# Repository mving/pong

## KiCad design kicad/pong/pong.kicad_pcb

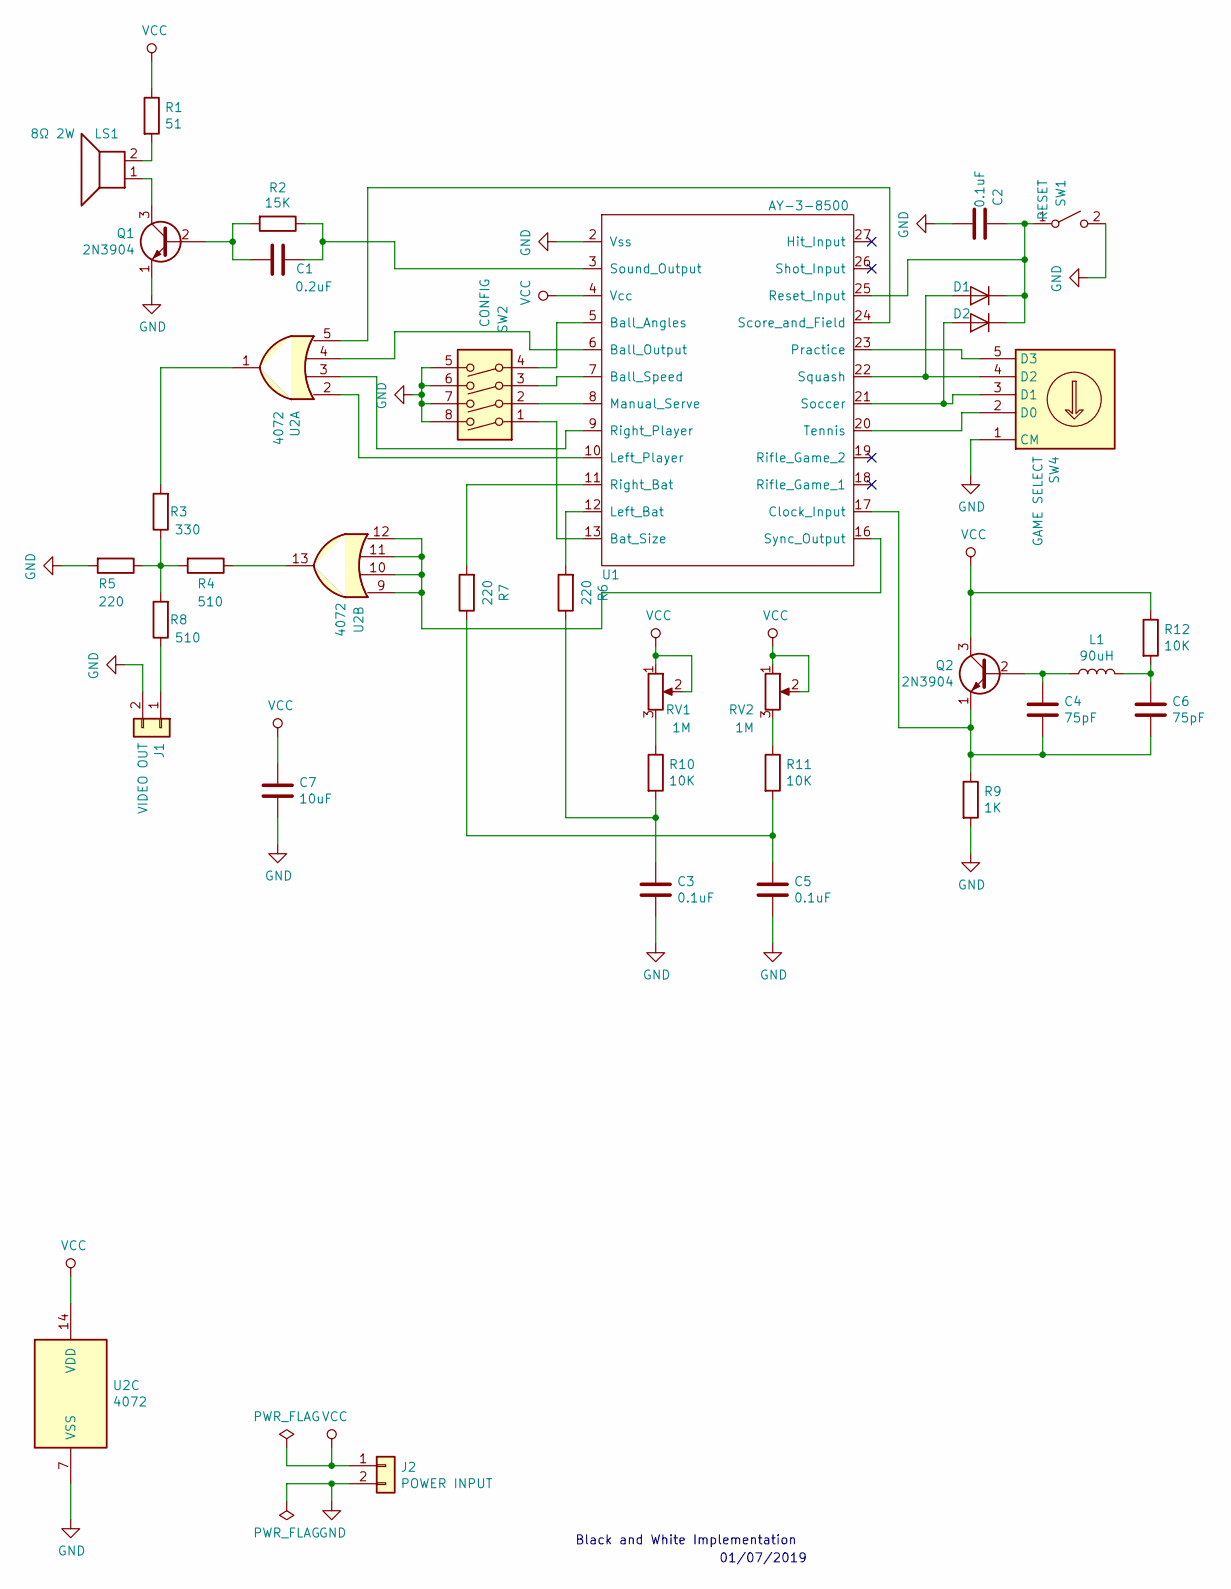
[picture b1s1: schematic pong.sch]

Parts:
C1: 0.2uF; C_Disc_D3.8mm_W2.6mm_P2.50mm
C2, C3, C5: 0.1uF; C_Disc_D3.8mm_W2.6mm_P2.50mm
C4, C6: 75pF; C_Disc_D3.8mm_W2.6mm_P2.50mm
C7: 10uF; C_Radial_D4.0mm_H5.0mm_P1.50mm
D1, D2: D; D_DO-35_SOD27_P7.62mm_Horizontal
J1: VIDEO OUT; rca_white
J2: POWER INPUT; BarrelJack_CUI_PJ-063AH_Horizontal
L1: 90uH; L_Axial_L5.3mm_D2.2mm_P10.16mm_Horizontal_Vishay_IM-1
LS1: 8Ω 2W; PinHeader_1x02_P2.00mm_Horizontal
Q1, Q2: 2N3904; TO-92_HandSolder
R1: 51; R_Axial_DIN0207_L6.3mm_D2.5mm_P7.62mm_Horizontal
R2: 15K; R_Axial_DIN0207_L6.3mm_D2.5mm_P7.62mm_Horizontal
R3: 330; R_Axial_DIN0207_L6.3mm_D2.5mm_P7.62mm_Horizontal
R4, R8: 510; R_Axial_DIN0207_L6.3mm_D2.5mm_P7.62mm_Horizontal
R5, R6, R7: 220; R_Axial_DIN0207_L6.3mm_D2.5mm_P7.62mm_Horizontal
R9: 1K; R_Axial_DIN0207_L6.3mm_D2.5mm_P7.62mm_Horizontal
R10, R11, R12: 10K; R_Axial_DIN0207_L6.3mm_D2.5mm_P7.62mm_Horizontal
RV1, RV2: 1M; PinHeader_1x03_P2.00mm_Horizontal
SW1: RESET; SW_PUSH_6mm_H4.3mm
SW2: CONFIG; SW_DIP_SPSTx04_Slide_9.78x12.34mm_W7.62mm_P2.54mm
SW4: GAME SELECT; PinHeader_1x05_P2.00mm_Horizontal
U1: AY-3-8500; DIP-28_W15.24mm_LongPads
U2: 4072; DIP-14_W7.62mm_LongPads

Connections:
GND: C2.1, C3.2, C5.2, C7.2, J1.2, J2.2, Q1.1 (E), R5.2, R9.2, SW1.2 (B), SW2.5, SW2.6, SW2.7, SW2.8, SW4.1 (CM), U1.2 (Vss), U2.7 (VSS)
unnamed: C1.1, R2.1, U1.3 (Sound_Output)
unnamed: C1.2, Q1.2 (B), R2.2
unnamed: C2.2, D1.1 (K), D2.1 (K), SW1.1 (A), U1.25 (Reset_Input)
unnamed: C3.1, R6.1, R10.2
unnamed: C4.1, L1.1, Q2.2 (B)
unnamed: C4.2, C6.2, Q2.1 (E), R9.1, U1.17 (Clock_Input)
unnamed: C5.1, R7.1, R11.2
unnamed: C6.1, L1.2, R12.2
unnamed: D1.2 (A), SW4.4 (D2), U1.22 (Squash)
unnamed: D2.2 (A), SW4.3 (D1), U1.21 (Soccer)
unnamed: J1.1, R8.1
unnamed: LS1.1, Q1.3 (C)
unnamed: LS1.2, R1.2
unnamed: R3.1, R4.2, R5.1, R8.2
unnamed: R3.2, U2.1
unnamed: R4.1, U2.13
unnamed: R6.2, U1.12 (Left_Bat)
unnamed: R7.2, U1.11 (Right_Bat)
unnamed: R10.1, RV1.3
unnamed: R11.1, RV2.3
unnamed: SW2.1, U1.13 (Bat_Size)
unnamed: SW2.2, U1.8 (Manual_Serve)
unnamed: SW2.3, U1.7 (Ball_Speed)
unnamed: SW2.4, U1.5 (Ball_Angles)
unnamed: SW4.2 (D0), U1.20 (Tennis)
unnamed: SW4.5 (D3), U1.23 (Practice)
unnamed: U1.6 (Ball_Output), U2.4
unnamed: U1.9 (Right_Player), U2.3
unnamed: U1.10 (Left_Player), U2.2
unnamed: U1.16 (Sync_Output), U2.9, U2.10, U2.11, U2.12
unnamed: U1.24 (Score_and_Field), U2.5
VCC: C7.1, J2.1, Q2.3 (C), R1.1, R12.1, RV1.1, RV1.2, RV2.1, RV2.2, U1.4 (Vcc), U2.14 (VDD)

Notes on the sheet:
01/07/2019
Black and White Implementation

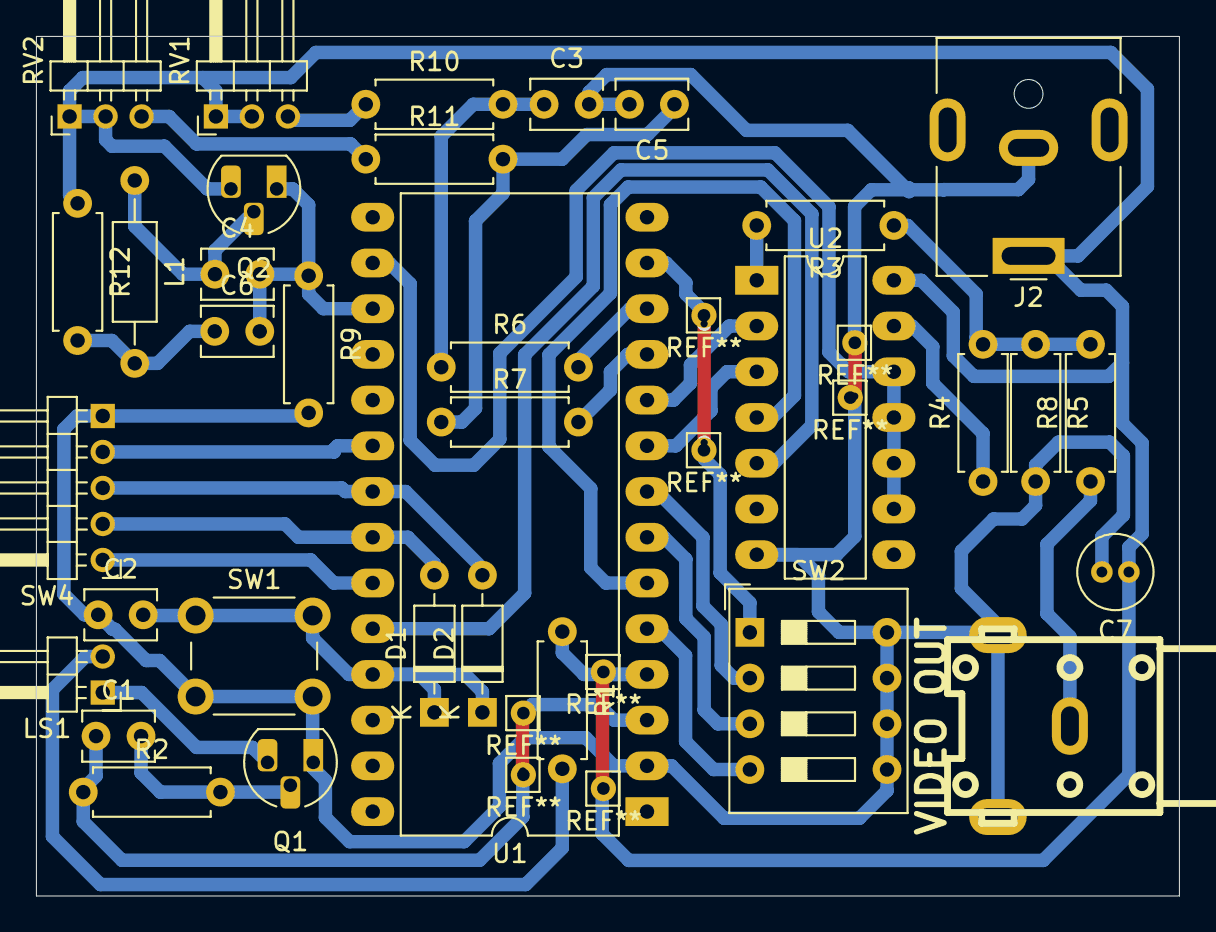
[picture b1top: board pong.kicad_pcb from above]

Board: 2 copper layers, 63.5 x 47.8 mm, 34 parts (0 on the bottom side), 33 nets.

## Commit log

2019-07-01 kicad
2019-07-01 Diagramas
2019-07-01 Render 3D
2019-07-01 Terminada
2019-07-01 En proceso
